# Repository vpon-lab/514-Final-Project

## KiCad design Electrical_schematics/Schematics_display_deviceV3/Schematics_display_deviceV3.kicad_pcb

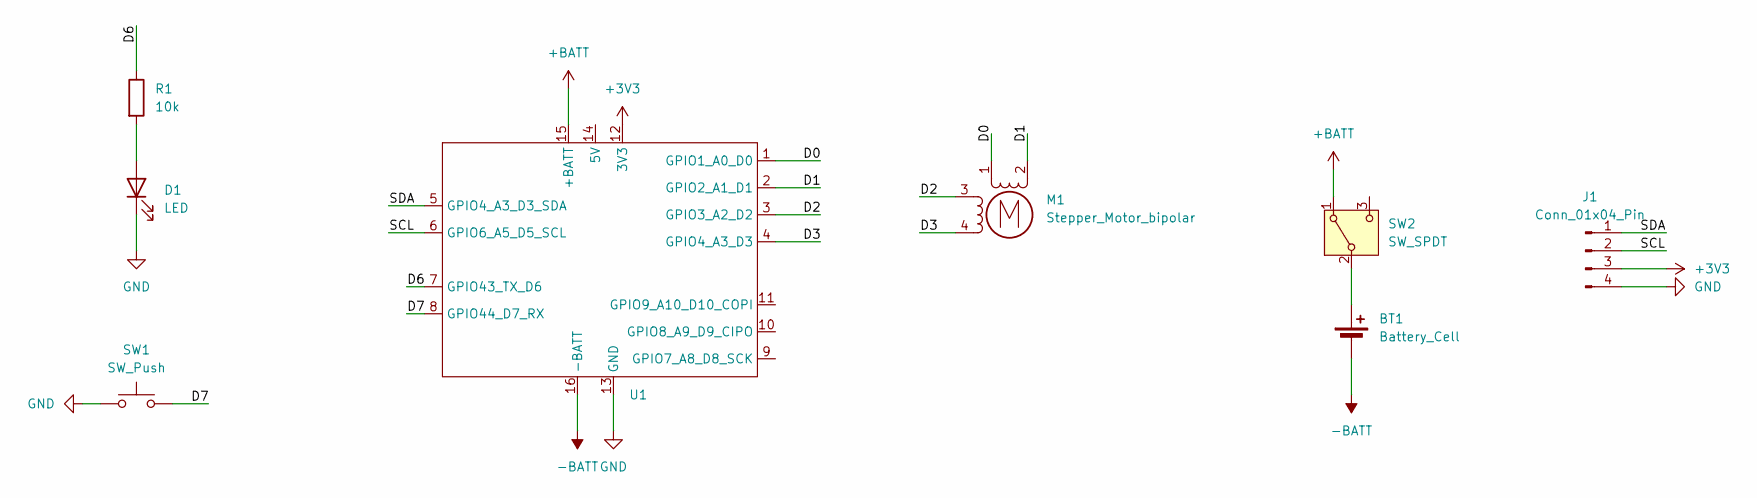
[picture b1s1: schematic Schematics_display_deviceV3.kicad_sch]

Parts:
BT1: Battery_Cell; JST_PH_B2B-PH-K_1x02_P2.00mm_Vertical
D1: LED; LED_0805_2012Metric_Pad1.15x1.40mm_HandSolder
J1: Conn_01x04_Pin; PinSocket_1x04_P2.54mm_Vertical
M1: Stepper_Motor_bipolar; x27_stepper
R1: 10k; R_0805_2012Metric_Pad1.20x1.40mm_HandSolder
SW1: SW_Push; SW_Push_1TS009xxxx-xxxx-xxxx_6x6x5mm
SW2: SW_SPDT; PinHeader_1x03_P2.54mm_Vertical
U1: XIAO_ESP32

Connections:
+3V3: J1.3, U1.12 (3V3)
+BATT: SW2.1 (A), U1.15 (+BATT)
-BATT: BT1.2 (-), U1.16 (-BATT)
/D0: M1.1, U1.1 (GPIO1_A0_D0)
/D1: M1.2 (-), U1.2 (GPIO2_A1_D1)
/D2: M1.3, U1.3 (GPIO3_A2_D2)
/D3: M1.4, U1.4 (GPIO4_A3_D3)
/D6: R1.1, U1.7 (GPIO43_TX_D6)
/D7: SW1.2, U1.8 (GPIO44_D7_RX)
/SCL: J1.2, U1.6 (GPIO6_A5_D5_SCL)
/SDA: J1.1, U1.5 (GPIO4_A3_D3_SDA)
GND: D1.1 (K), J1.4, SW1.1, U1.13 (GND)
unnamed: BT1.1 (+), SW2.2 (B)
unnamed: D1.2 (A), R1.2

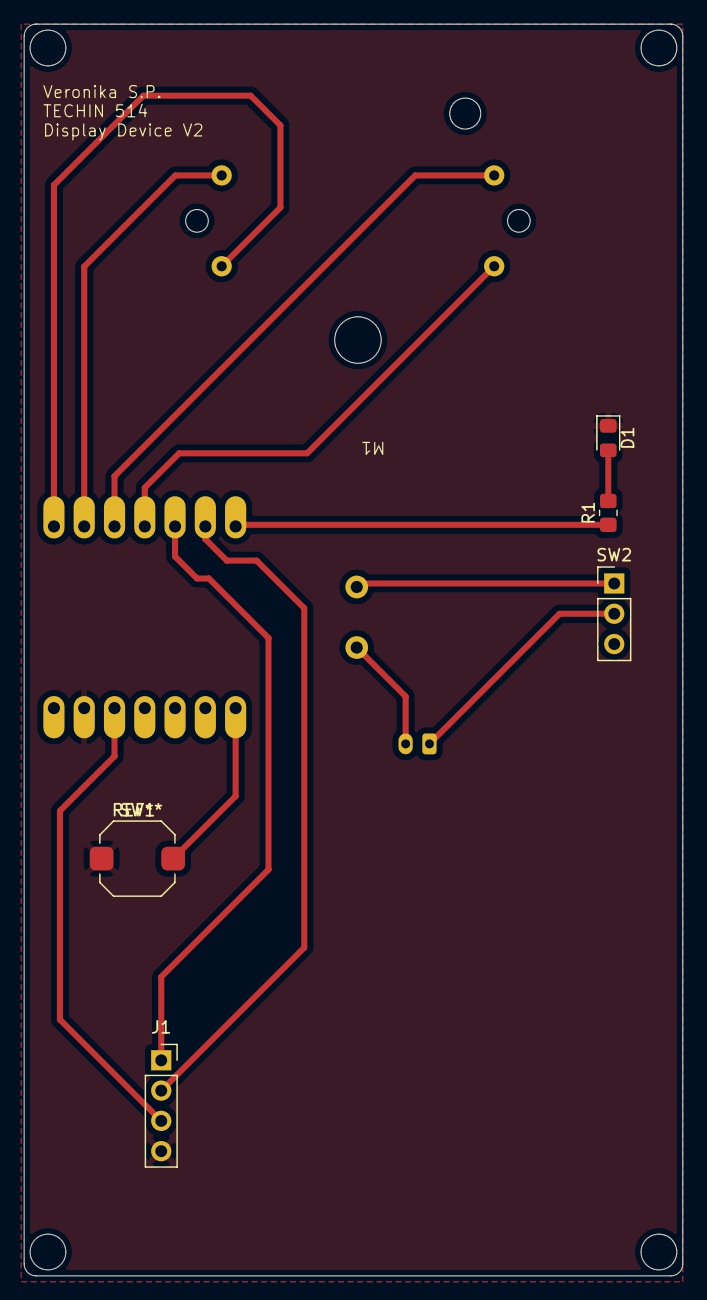
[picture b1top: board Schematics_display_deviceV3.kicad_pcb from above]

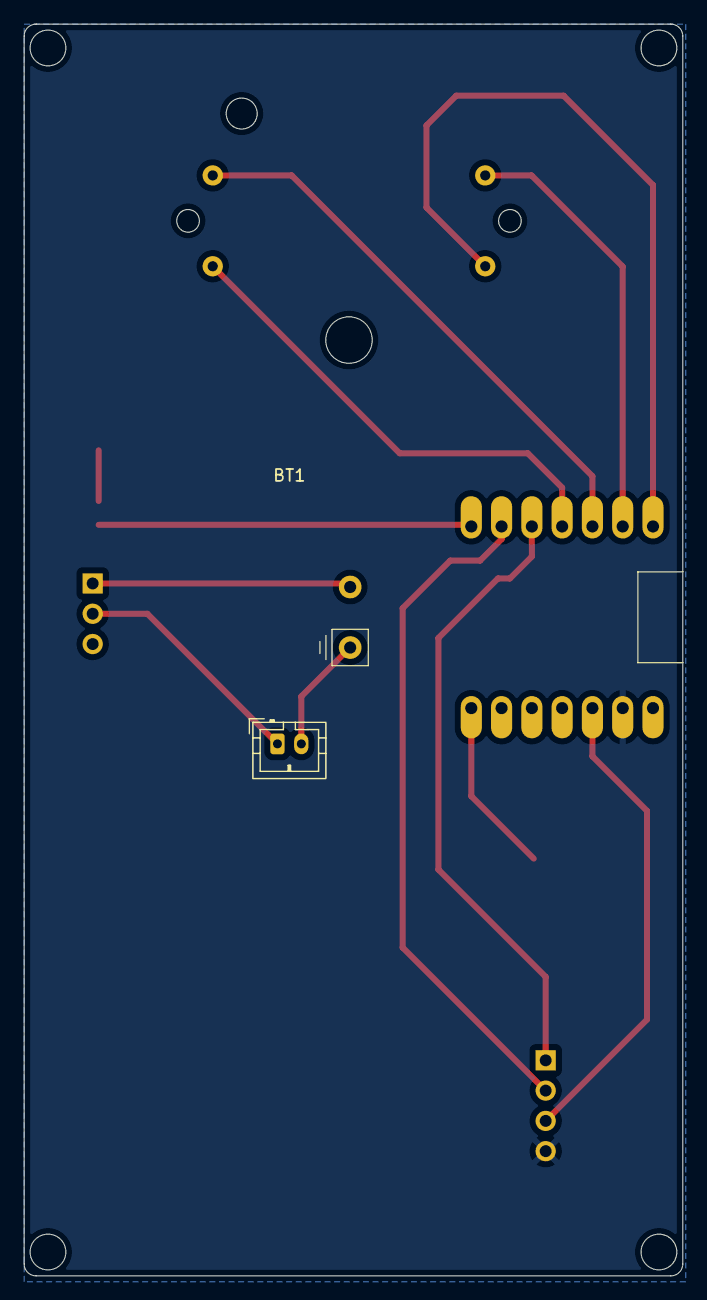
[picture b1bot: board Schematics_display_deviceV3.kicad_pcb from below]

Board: 2 copper layers, 55.2 x 105.0 mm, 8 parts (2 on the bottom side), 14 nets.

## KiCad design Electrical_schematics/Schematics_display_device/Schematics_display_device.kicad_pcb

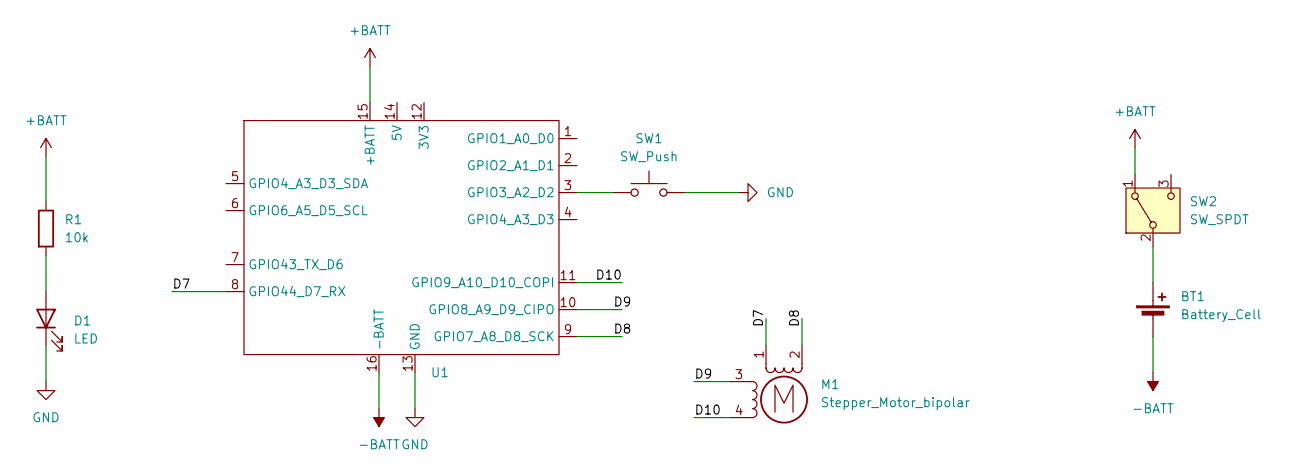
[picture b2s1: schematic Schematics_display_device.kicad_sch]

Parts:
BT1: Battery_Cell; JST_PH_B2B-PH-K_1x02_P2.00mm_Vertical
D1: LED; LED_0805_2012Metric_Pad1.15x1.40mm_HandSolder
M1: Stepper_Motor_bipolar; x27_stepper
R1: 10k; R_0805_2012Metric_Pad1.20x1.40mm_HandSolder
SW1: SW_Push; SW_Push_1TS009xxxx-xxxx-xxxx_6x6x5mm
SW2: SW_SPDT; PinHeader_1x03_P2.54mm_Vertical
U1: XIAO_ESP32

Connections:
+BATT: R1.1, SW2.1 (A), U1.15 (+BATT)
-BATT: BT1.2 (-), U1.16 (-BATT)
/D7: M1.1, U1.8 (GPIO44_D7_RX)
/D8: M1.2 (-), U1.9 (GPIO7_A8_D8_SCK)
/D9: M1.3, U1.10 (GPIO8_A9_D9_CIPO)
/D10: M1.4, U1.11 (GPIO9_A10_D10_COPI)
GND: D1.1 (K), SW1.2, U1.13 (GND)
unnamed: BT1.1 (+), SW2.2 (B)
unnamed: D1.2 (A), R1.2
unnamed: SW1.1, U1.3 (GPIO3_A2_D2)

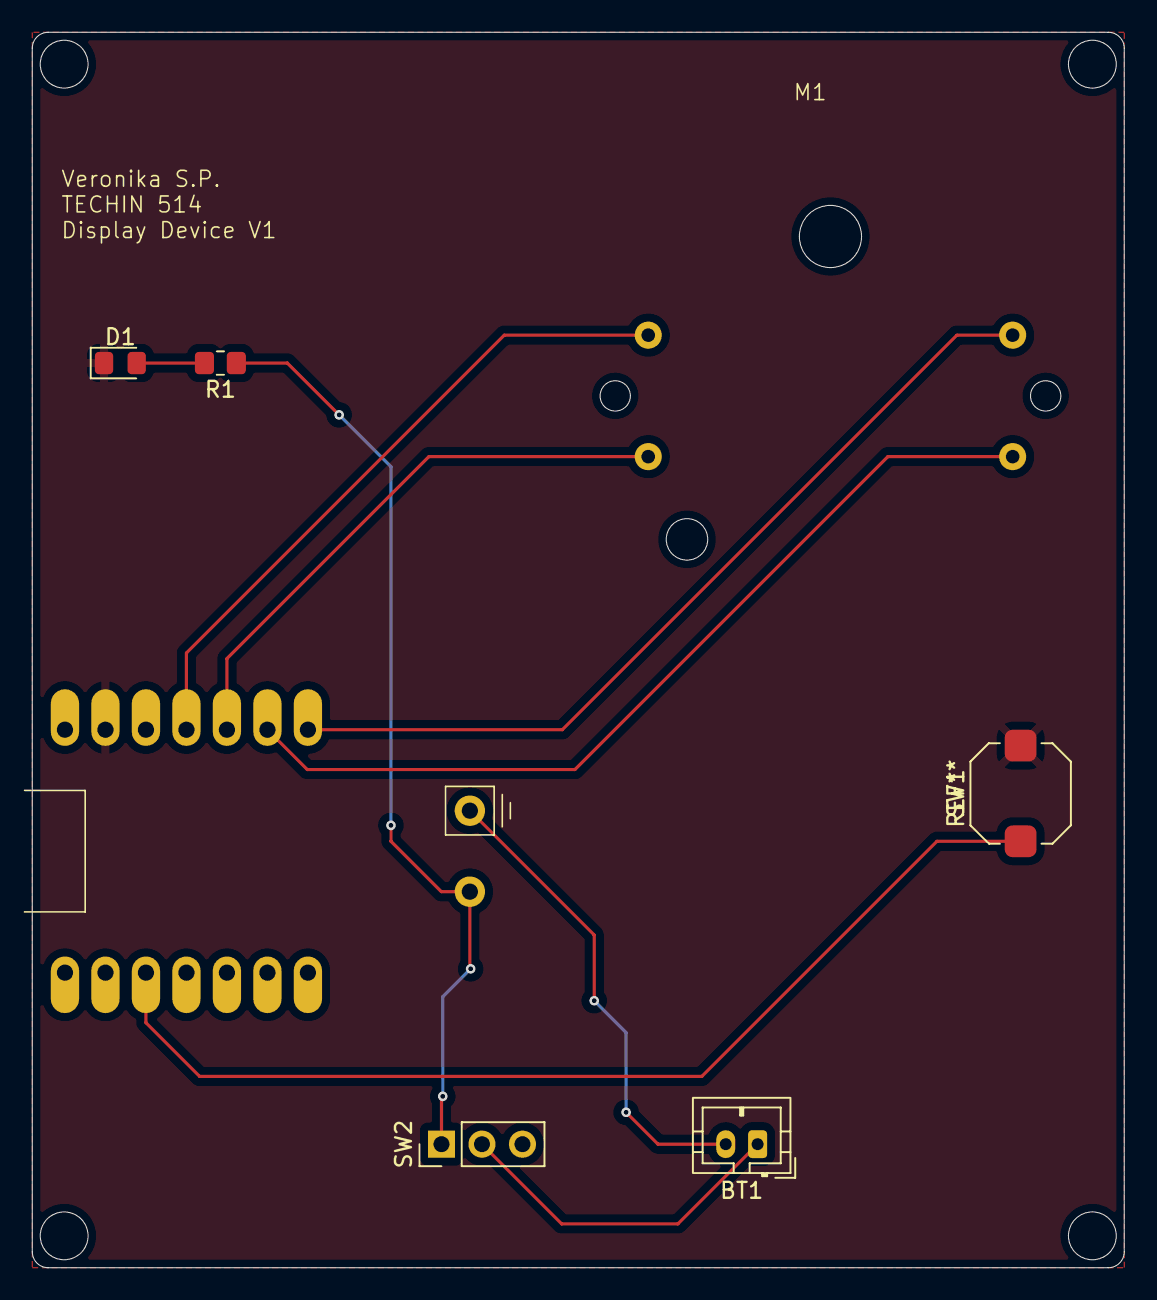
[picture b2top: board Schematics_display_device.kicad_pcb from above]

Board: 2 copper layers, 68.5 x 77.5 mm, 7 parts (0 on the bottom side), 10 nets.

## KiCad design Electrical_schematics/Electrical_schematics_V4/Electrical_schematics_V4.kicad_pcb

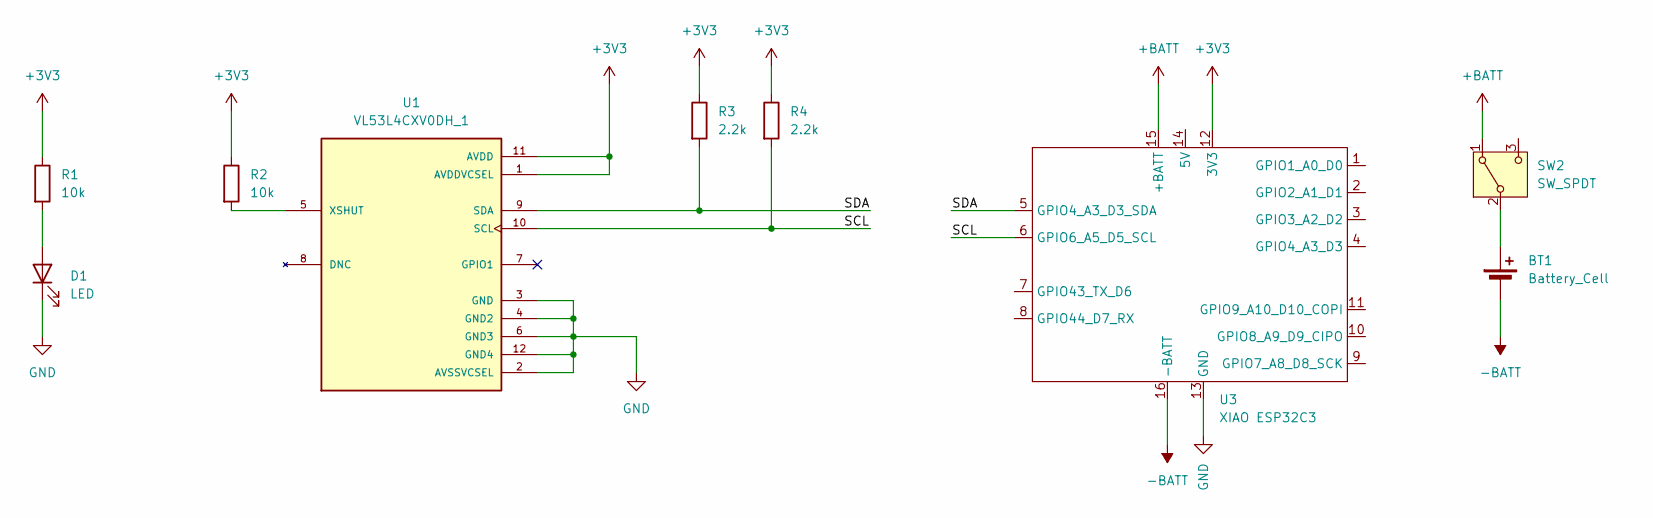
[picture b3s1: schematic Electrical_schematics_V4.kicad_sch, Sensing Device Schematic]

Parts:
BT1: Battery_Cell; JST_PH_B2B-PH-K_1x02_P2.00mm_Vertical
D1: LED; LED_0805_2012Metric_Pad1.15x1.40mm_HandSolder
R1, R2: 10k; R_0805_2012Metric_Pad1.20x1.40mm_HandSolder
R3, R4: 2.2k; R_0805_2012Metric_Pad1.20x1.40mm_HandSolder
SW2: SW_SPDT; PinHeader_1x03_P2.54mm_Vertical
U1: VL53L4CXV0DH_1; XCDR_VL53L4CXV0DH_1; PARTREV 4
U3: XIAO ESP32C3; XIAO_ESP32

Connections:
+3V3: R1.1, R2.1, R3.1, R4.1, U1.1 (AVDDVCSEL), U1.11 (AVDD), U3.12 (3V3)
+BATT: SW2.1 (A), U3.15 (+BATT)
-BATT: BT1.2 (-), U3.16 (-BATT)
/SCL: R4.2, U1.10 (SCL), U3.6 (GPIO6_A5_D5_SCL)
/SDA: R3.2, U1.9 (SDA), U3.5 (GPIO4_A3_D3_SDA)
GND: D1.1 (K), U1.2 (AVSSVCSEL), U1.3 (GND), U1.4 (GND2), U1.6 (GND3), U1.12 (GND4), U3.13 (GND)
unnamed: BT1.1 (+), SW2.2 (B)
unnamed: D1.2 (A), R1.2
unnamed: R2.2, U1.5 (XSHUT)

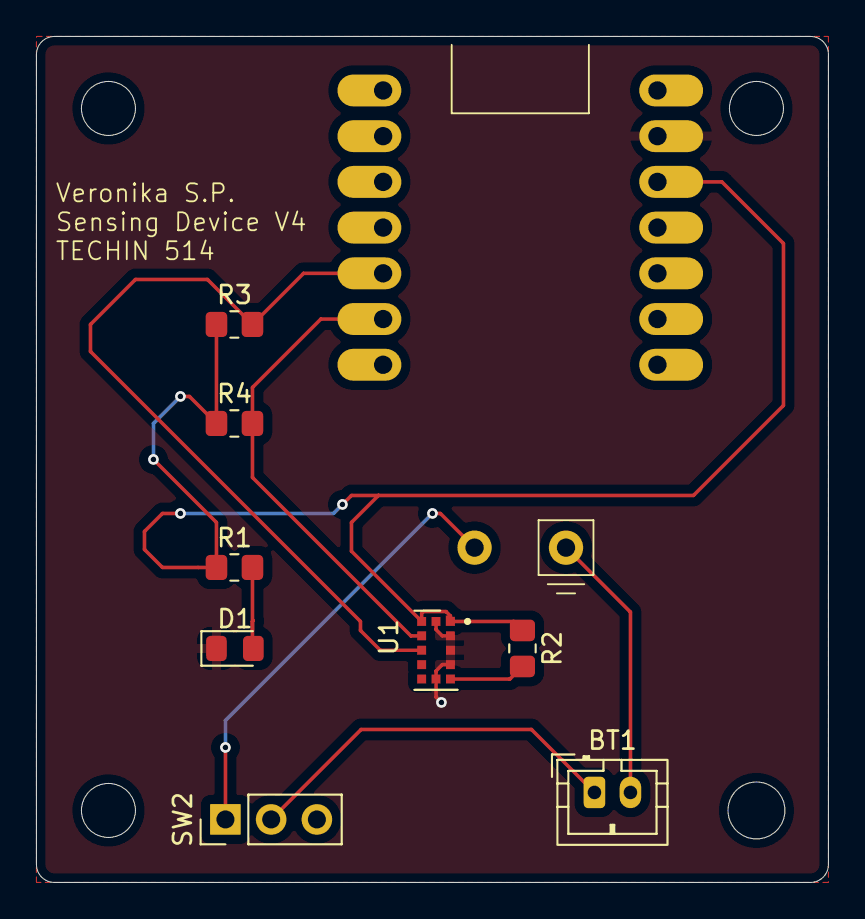
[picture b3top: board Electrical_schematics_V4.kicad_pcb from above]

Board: 2 copper layers, 44.0 x 47.0 mm, 9 parts (0 on the bottom side), 9 nets.

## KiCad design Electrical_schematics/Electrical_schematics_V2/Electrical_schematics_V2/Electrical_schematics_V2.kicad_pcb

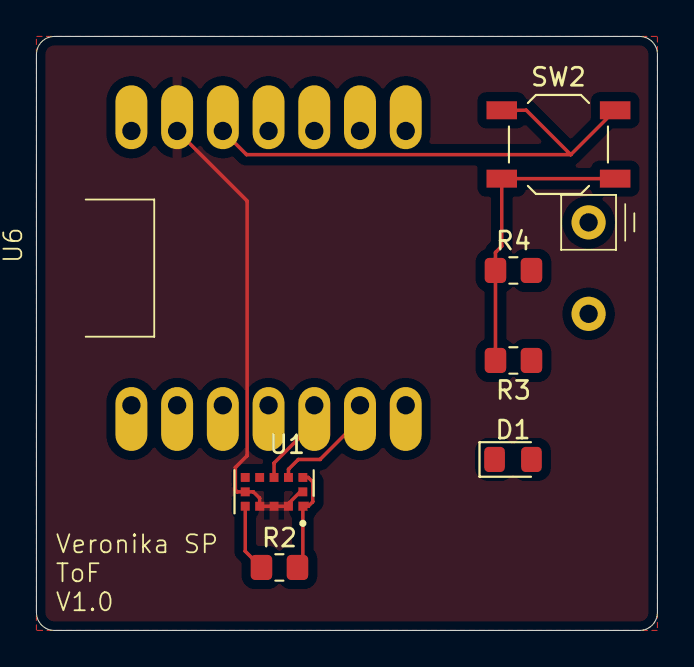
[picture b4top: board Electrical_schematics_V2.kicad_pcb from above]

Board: 2 copper layers, 34.5 x 33.0 mm, 7 parts (0 on the bottom side), 7 nets.

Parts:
D1: GREEN; LED_0805_2012Metric_Pad1.15x1.40mm_HandSolder
R2, R3: 10K; R_0805_2012Metric_Pad1.20x1.40mm_HandSolder
R4: 3.6K; R_0805_2012Metric_Pad1.20x1.40mm_HandSolder
SW2: SW_Push; SW_SPST_TL3342
U1: VL53L4CXV0DH_1; XCDR_VL53L4CXV0DH_1
U6: XIAO ESP32C3; XIAO_ESP32

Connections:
3.3V: R2.2, U1.1 (AVDDVCSEL), U1.11 (AVDD)
/SCL: U1.10 (SCL), U6.6 (D5)
/SDA: U1.9 (SDA), U6.5 (D4)
/XSHUT_2.8V: R2.1, U1.5 (XSHUT)
GND: U1.2 (AVSSVCSEL), U1.3 (GND), U1.4 (GND2), U1.6 (GND3), U1.12 (GND4), U6.13 (GND)
unnamed: SW2.1, U6.12 (VCC_3V3)
VCC: R3.2, R4.1, SW2.2

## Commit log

2026-01-20 Initial commit, added README.md file to system architecture assignment repo
2026-01-20 Added sections
2026-01-20 added a template descriptions to guide me on what to write
2026-01-20 Description sentences are done
2026-01-20 Sketches and block diagrams implemented
2026-01-20 added datasheets
2026-01-20 pdf update and README revisions in System Overview section
2026-01-27 Added schematics, and made a BOM to the best of my abilities.
2026-01-27 updating system architecture in minor details. (touch ups)
2026-01-27 changing battery value because voltage is unknown need help figuring that out
2026-01-27 updated pdf for system architecture and pdf for schematics
2026-02-09 I've added data sheets and made a 2nd version of my schematic a while ago I think I forgot to commit
2026-02-09 adding excel sheet of Battery Life Estimate into github repo
2026-02-20 file changes to PCB version history
2026-02-23 added data sheets and new version of sensing schematic
2026-03-01 added datasheets, new schematics, and displaydevice project
2026-03-05 added 2nd version of schematics of display device
2026-03-09 display device code furnished. Improvements can be made after making enclosure.
2026-03-16 display and sensing device code done. Added presentation slides.
2026-03-16 updated power model for sensing device
2026-03-16 edited presentation, added power model for display device
